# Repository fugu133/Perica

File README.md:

# シングルチャンネル・ハイパワーモータードライバ PERICA

## 概要
PERICAは色々できる小型モータドライバです．
* CW, CCW, Brake, Coastの出力制御
* デジタル部とパワー部を完全に絶縁
* RS-485による通信
* Arduino Uno (Nano)に互換
* 直接ロータリーエンコーダを接続可能

当時，ケーブルを作る資金と時間の余裕がなかった為  
SATAケーブルで通信を行うという珍しい設計になっています．

## 作成例

## 動作例
<video controls width="320" src="https://user-images.githubusercontent.com/62766332/225111963-716b9bb1-7227-4d82-8061-c68b7f025649.mp4"></video>

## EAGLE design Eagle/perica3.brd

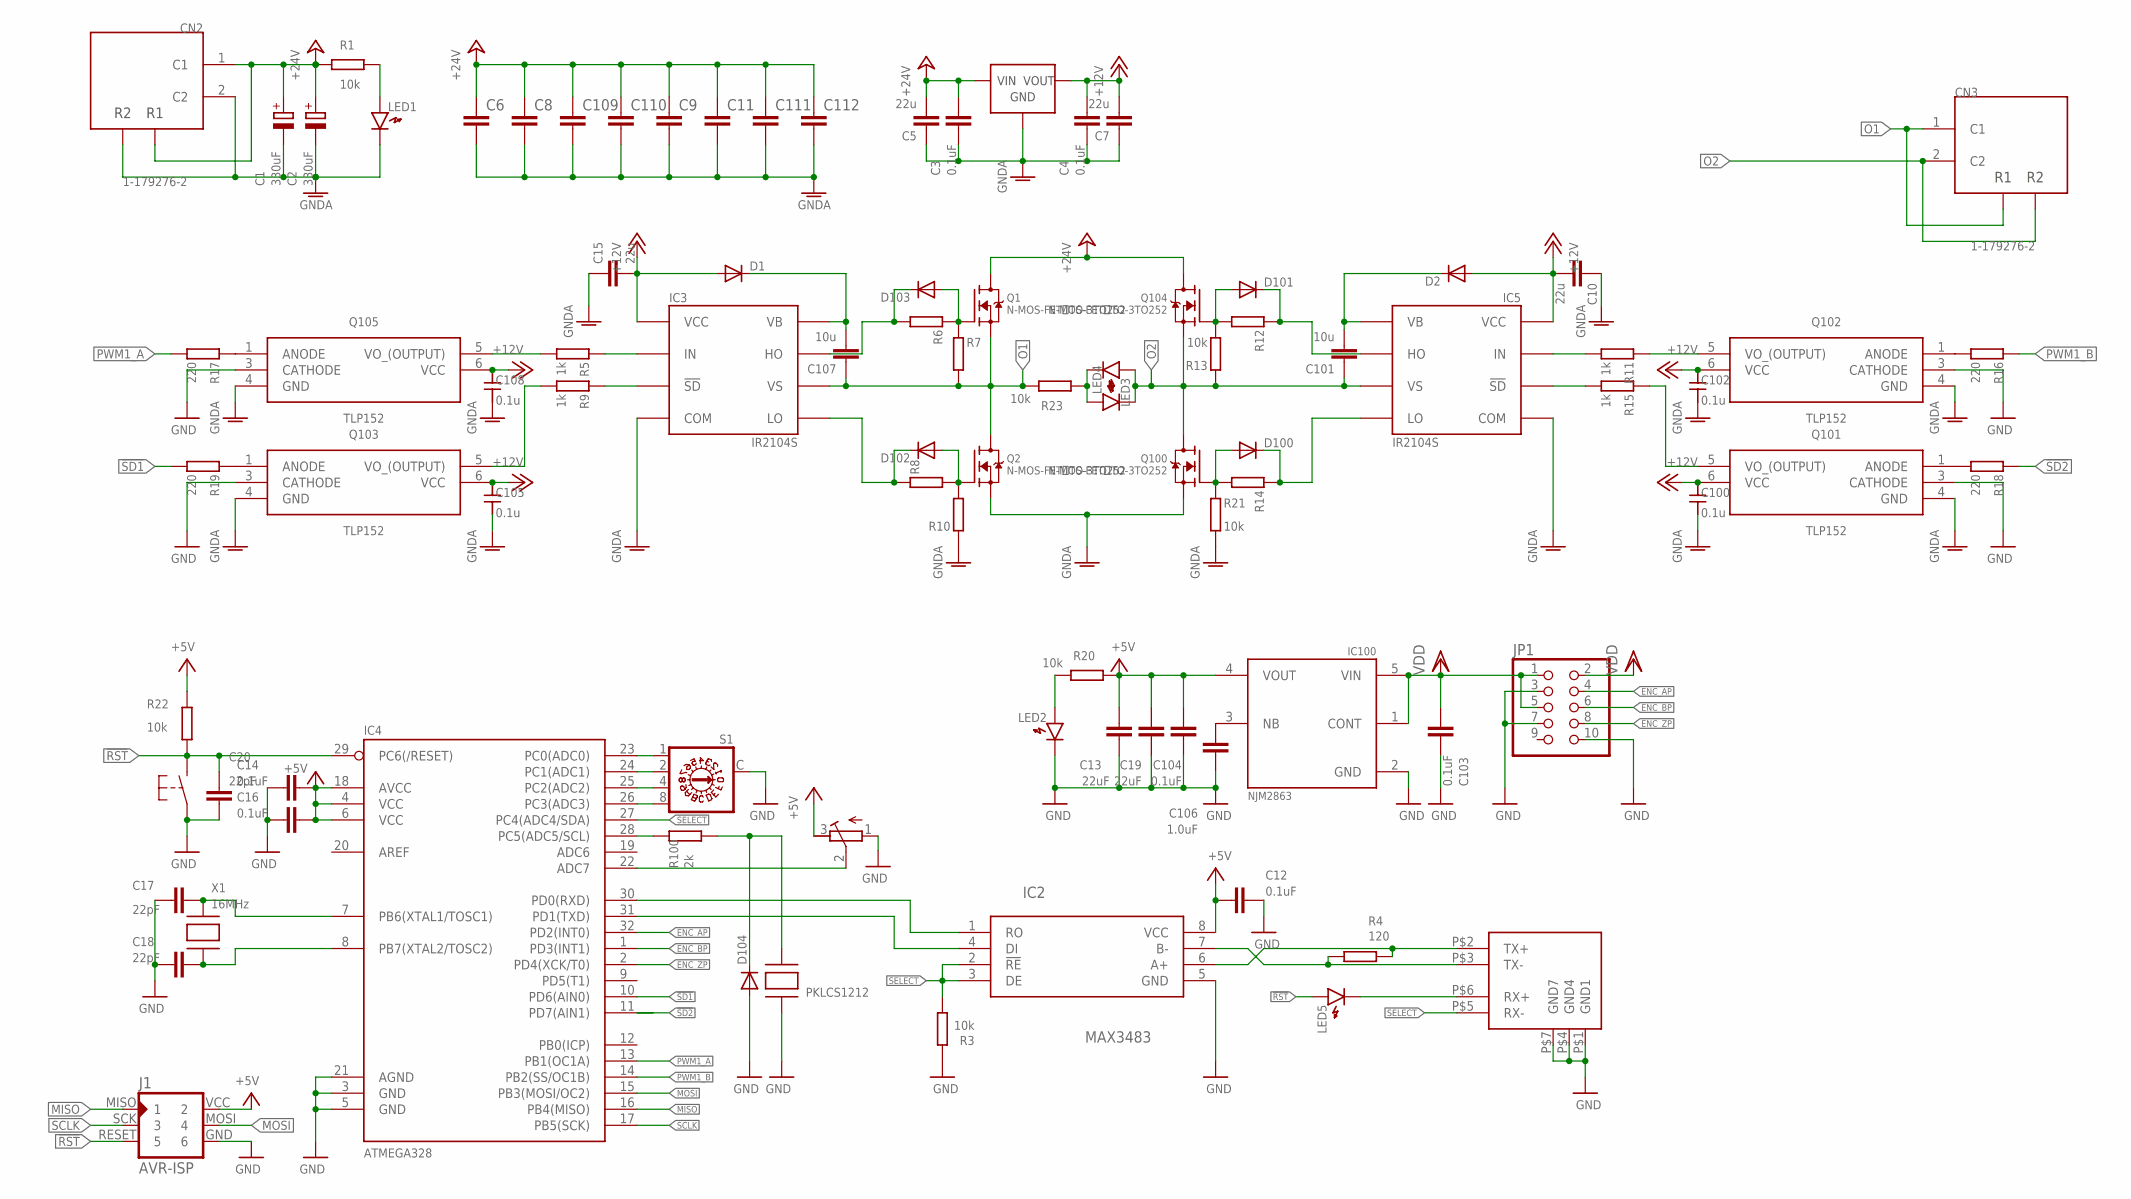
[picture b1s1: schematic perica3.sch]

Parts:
C1, C2: 330uF; UD-10X10_NICHICON
C3, C4, C12, C14, C16, C103, C104: 0.1uF; C0603K
C5, C7, C10, C15: 22u; C1206K
C6, C8, C9, C11, C109, C110, C111, C112: C-EUC1206; C1206
C13, C19: 22uF; C0805K
C17, C18, C20: 22pF; C0603K
C100, C102, C105, C108: 0.1u; SMD1608
C101, C107: 10u; C1206K
C106: 1.0uF; C0603K
CN1: SATA; SATA_MOLEX_LLC_0470804001
CN2, CN3: 1-179276-2
D1, D2, D100, D101, D102, D103, D104: DIODE-SOD123; SOD123
IC1: NJM78XX; TO252
IC2: MAX3483; SO-8
IC3, IC5: IR2104S; SO-8
IC4: ATMEGA328; TQFP32-08
IC100: NJM2863; SOT-23-5
J1: AVR-ISP; AVR-ISP-6PIN-SMAILL-SILK
JP1: PINHD-2X5; 2X05
LED1, LED2, LED3, LED4, LED5: RED; LED_1608
Q1, Q2, Q100, Q104: N-MOS-FETーTO-3TO252; TO252
Q101, Q102, Q103, Q105: TLP152; 11-4L1S(5-PIN-SOIC)
R1, R3, R13, R20, R21, R22, R23: 10k; SMD1608
R2: 10k-20k; RTRIM4G/J
R4: 120; SMD1608
R5, R9, R11, R15: 1k; SMD1608
R6, R7, R8, R10, R12, R14: REGISTER1068; SMD1608
R16, R17, R18, R19: 220; SMD1608
R100: 2k; SMD1608
S1: P103
SW1: TUCT_SW_MINI; SW1
X1: 16MHz; NX5032
Z1: PKLCS1212

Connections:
!RST: C20.2, IC4.29 (PC6(/RESET)), J1.RESET (5), LED5.A, R22.1, SW1.P$2 (S)
!SD1: IC4.10 (PD6(AIN0)), R19.2
!SD2: IC4.11 (PD7(AIN1)), R18.1
+5V: C12.2, C13.1, C14.2, C16.2, C19.1, C104.2, IC2.8 (VCC), IC4.4 (VCC), IC4.6 (VCC), IC4.18 (AVCC), IC100.4 (VOUT), J1.VCC (2), R2.3 (E), R20.2, R22.2
+12V: C4.2, C7.2, C10.2, C15.2, C100.1, C102.1, C105.1, C108.1, D1.A, D2.A, IC1.2 (VOUT), IC3.1 (VCC), IC5.1 (VCC), Q101.6 (VCC), Q102.6 (VCC), Q103.6 (VCC), Q105.6 (VCC)
+24V: C1.+, C2.+, C3.2, C5.2, C6.1, C8.1, C9.1, C11.1, C109.1, C110.1, C111.1, C112.1, CN2.1 (C1), CN2.4 (R1), IC1.1 (VIN), Q1.3 (D), Q104.3 (D), R1.2
ENC_AP: IC4.32 (PD2(INT0)), JP1.4
ENC_BP: IC4.1 (PD3(INT1)), JP1.6
ENC_ZP: IC4.2 (PD4(XCK/T0)), JP1.8
G1_HIS: D103.A, Q1.1 (G), R6.1, R7.1
G1_LOS: D100.A, Q100.1 (G), R14.2, R21.1
G2_HIS: D101.A, Q104.1 (G), R12.2, R13.2
G2_LOS: D102.A, Q2.1 (G), R8.2, R10.2
GND: C12.1, C13.2, C14.1, C16.1, C17.1, C18.1, C19.2, C20.1, C103.1, C104.1, C106.1, CN1.P$1 (GND1), CN1.P$4 (GND4), CN1.P$7 (GND7), D104.A, IC2.5 (GND), IC4.3 (GND), IC4.5 (GND), IC4.21 (AGND), IC100.2 (GND), J1.GND (6), JP1.3, JP1.7, JP1.10, LED2.K, Q101.3 (CATHODE), Q102.3 (CATHODE), Q103.3 (CATHODE), Q105.3 (CATHODE), R2.1 (A), R3.2, S1.C, SW1.P$1, Z1.P$2
GNDA: C1.-, C2.-, C3.1, C4.1, C5.1, C6.2, C7.1, C8.2, C9.2, C10.1, C11.2, C15.1, C100.2, C102.2, C105.2, C108.2, C109.2, C110.2, C111.2, C112.2, CN2.2 (C2), CN2.3 (R2), IC1.3 (GND), IC3.4 (COM), IC5.4 (COM), LED1.K, Q2.2 (S), Q100.2 (S), Q101.4 (GND), Q102.4 (GND), Q103.4 (GND), Q105.4 (GND), R10.1, R21.2
MISO: IC4.16 (PB4(MISO)), J1.MISO (1)
MOSI: IC4.15 (PB3(MOSI/OC2)), J1.MOSI (4)
unnamed: IC3.2 (IN), R5.1
unnamed: IC4.26 (PC3(ADC3)), S1.8
unnamed: IC4.25 (PC2(ADC2)), S1.4
unnamed: C107.2, D1.C, IC3.8 (VB)
unnamed: D103.C, IC3.7 (HO), R6.2
unnamed: C17.2, IC4.7 (PB6(XTAL1/TOSC1)), X1.P$2
unnamed: C18.2, IC4.8 (PB7(XTAL2/TOSC2)), X1.P$1
unnamed: D101.C, IC5.7 (HO), R12.1
unnamed: IC4.24 (PC1(ADC1)), S1.2
unnamed: D100.C, IC5.5 (LO), R14.1
unnamed: D102.C, IC3.5 (LO), R8.1
unnamed: IC4.23 (PC0(ADC0)), S1.1
unnamed: C101.2, D2.C, IC5.8 (VB)
unnamed: IC3.3 (!SD), R9.1
unnamed: IC5.2 (IN), R11.2
unnamed: IC5.3 (!SD), R15.2
unnamed: Q105.1 (ANODE), R17.1
unnamed: Q102.5 (VO_(OUTPUT)), R11.1
unnamed: Q101.5 (VO_(OUTPUT)), R15.1
unnamed: Q105.5 (VO_(OUTPUT)), R5.2
unnamed: Q103.5 (VO_(OUTPUT)), R9.2
unnamed: Q103.1 (ANODE), R19.1
unnamed: Q102.1 (ANODE), R16.2
unnamed: Q101.1 (ANODE), R18.2
unnamed: IC4.28 (PC5(ADC5/SCL)), R100.2
unnamed: D104.C, R100.1, Z1.P$1
unnamed: LED2.A, R20.1
unnamed: CN1.P$6 (RX+), LED5.K
unnamed: C106.2, IC100.3 (NB)
unnamed: LED1.A, R1.1
unnamed: CN1.P$2 (TX+), IC2.6 (A+), R4.1
unnamed: LED3.K, LED4.A, R23.2
unnamed: IC4.22 (ADC7), R2.2 (S)
unnamed: CN1.P$3 (TX-), IC2.7 (B-), R4.2
O1: C107.1, CN3.1 (C1), CN3.4 (R1), IC3.6 (VS), Q1.2 (S), Q2.3 (D), R7.2, R23.1
O2: C101.1, CN3.2 (C2), CN3.3 (R2), IC5.6 (VS), LED3.A, LED4.K, Q100.3 (D), Q104.2 (S), R13.1
PWM1_A: IC4.13 (PB1(OC1A)), R17.2
PWM1_B: IC4.14 (PB2(SS/OC1B)), R16.1
RXD: IC2.4 (DI), IC4.31 (PD1(TXD))
SCLK: IC4.17 (PB5(SCK)), J1.SCK (3)
SELECT: CN1.P$5 (RX-), IC2.2 (!RE), IC2.3 (DE), IC4.27 (PC4(ADC4/SDA)), R3.1
TXD: IC2.1 (RO), IC4.30 (PD0(RXD))
VDD: C103.2, IC100.1 (CONT), IC100.5 (VIN), JP1.1, JP1.2, JP1.5

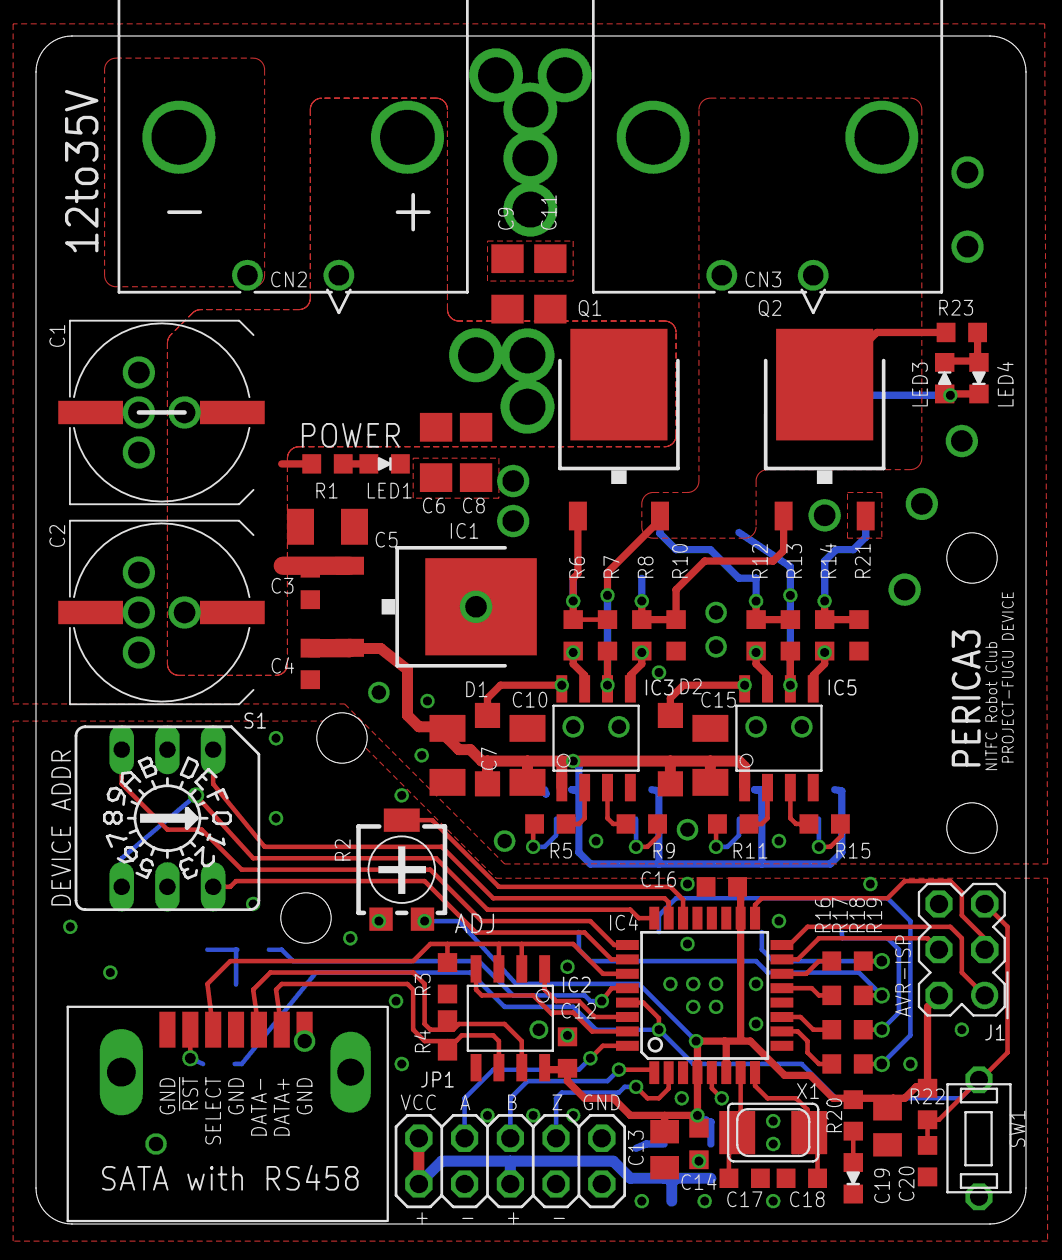
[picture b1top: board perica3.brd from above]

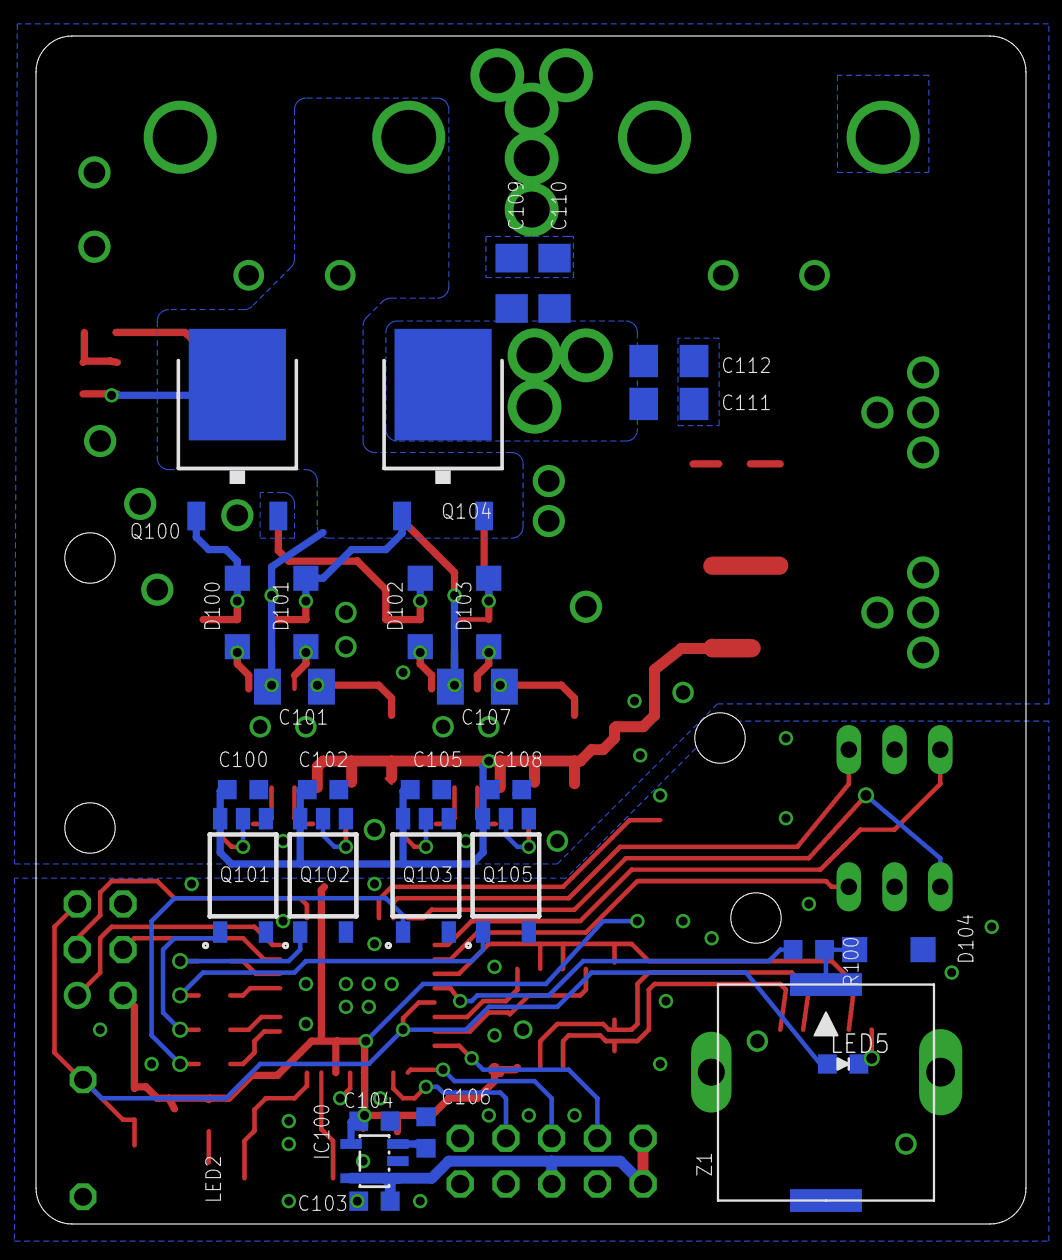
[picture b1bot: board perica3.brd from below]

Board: 2 copper layers, 55.0 x 66.0 mm, 92 parts (28 on the bottom side), 60 nets.

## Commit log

2023-02-28 設計ファイルを追加
2023-02-28 READMEを変更
2023-03-02 不要ファイルを削除
